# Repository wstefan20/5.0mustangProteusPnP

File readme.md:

# 5.0 Mustang Proteus PnP
PnP adapter board for 5.0 mustang EEC-IV computer using Proteus Rusefi v0.5 compatible board.

This board is designed as both a PnP stock replacement for the A9L/A9P EECs found in 5.0 manual foxbody mustangs, as well as a fully featured aftermarket ECU. This board is designed to fit into BOTH versions of the stock Ford EEC-IV case.

PLEASE do not rip apart any A9L computers to house this unit, there's very few of them left and they sell for a lot! Keep or sell that and buy any late 80s to early 90s EEC-IV as a donor instead such as 88 ford taurus 2.4 EEC for $25.

wiki and more info coming after fully tested.

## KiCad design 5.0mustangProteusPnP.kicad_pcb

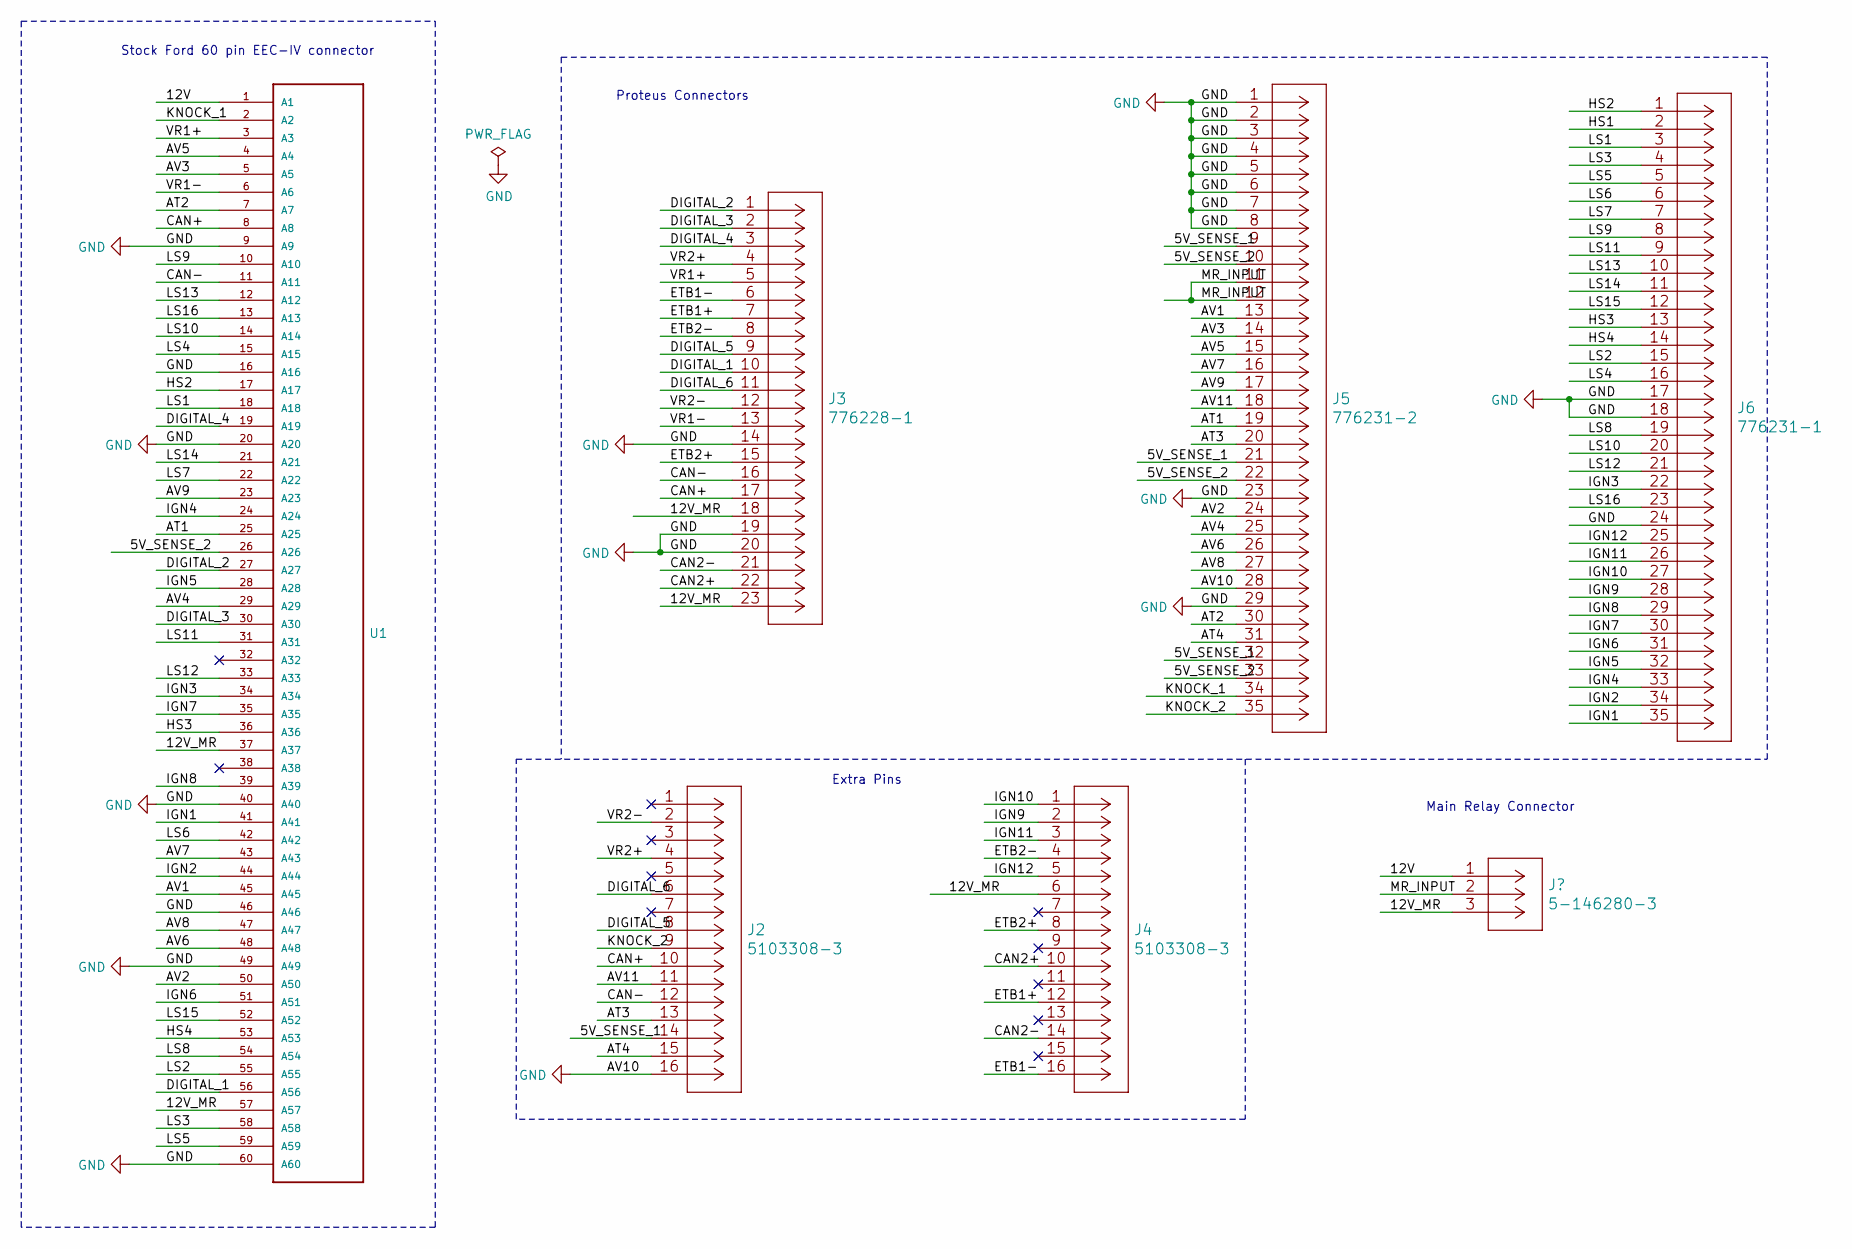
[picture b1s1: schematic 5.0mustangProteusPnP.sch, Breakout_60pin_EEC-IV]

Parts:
J2, J4: 5103308-3
J3: 776228-1
J5: 776231-2
J6: 776231-1
U1: FORD60PIN

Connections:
/5V_SENSE_1: J2.14, J5.9, J5.21, J5.32
/5V_SENSE_2: J5.10, J5.22, J5.33, U1.26 (A26)
/12V: U1.1 (A1); also elsewhere on the board
/12V_MR: J3.18, J3.23, J4.6, U1.37 (A37), U1.57 (A57); also elsewhere on the board
/AT1: J5.19, U1.25 (A25)
/AT2: J5.30, U1.7 (A7)
/AT3: J2.13, J5.20
/AT4: J2.15, J5.31
/AV1: J5.13, U1.45 (A45)
/AV2: J5.24, U1.50 (A50)
/AV3: J5.14, U1.5 (A5)
/AV4: J5.25, U1.29 (A29)
/AV5: J5.15, U1.4 (A4)
/AV6: J5.26, U1.48 (A48)
/AV7: J5.16, U1.43 (A43)
/AV8: J5.27, U1.47 (A47)
/AV9: J5.17, U1.23 (A23)
/AV11: J2.11, J5.18
/CAN2+: J3.22, J4.10
/CAN2-: J3.21, J4.14
/CAN+: J2.10, J3.17, U1.8 (A8)
/CAN-: J2.12, J3.16, U1.11 (A11)
/DIGITAL_1: J3.10, U1.56 (A56)
/DIGITAL_2: J3.1, U1.27 (A27)
/DIGITAL_3: J3.2, U1.30 (A30)
/DIGITAL_4: J3.3, U1.19 (A19)
/DIGITAL_5: J2.8, J3.9
/DIGITAL_6: J2.6, J3.11
/ETB1+: J3.7, J4.12
/ETB1-: J3.6, J4.16
/ETB2+: J3.15, J4.8
/ETB2-: J3.8, J4.4
/HS1: J2.1, J6.2
/HS3: J6.13, U1.36 (A36)
/HS4: J6.14, U1.53 (A53)
/IGN1: J6.35, U1.41 (A41)
/IGN2: J6.34, U1.44 (A44)
/IGN3: J6.22, U1.34 (A34)
/IGN4: J6.33, U1.24 (A24)
/IGN5: J6.32, U1.28 (A28)
/IGN6: J6.31, U1.51 (A51)
/IGN7: J6.30, U1.35 (A35)
/IGN8: J6.29, U1.39 (A39)
/IGN9: J4.2, J6.28
/IGN10: J4.1, J6.27
/IGN11: J4.3, J6.26
/IGN12: J4.5, J6.25
/KNOCK_1: J5.34, U1.2 (A2)
/KNOCK_2: J2.9, J5.35
/LS1: J6.3, U1.18 (A18)
/LS2: J6.15, U1.55 (A55)
/LS3: J6.4, U1.58 (A58)
/LS4: J6.16, U1.15 (A15)
/LS5: J6.5, U1.59 (A59)
/LS6: J6.6, U1.42 (A42)
/LS7: J6.7, U1.22 (A22)
/LS8: J6.19, U1.54 (A54)
/LS9: J6.8, U1.10 (A10)
/LS10: J6.20, U1.14 (A14)
/LS11: J6.9, U1.31 (A31)
/LS13: J6.10, U1.12 (A12)
/LS14: J6.11, U1.21 (A21)
/LS15: J6.12, U1.52 (A52)
/LS16: J6.23, U1.13 (A13)
/MR_INPUT: J5.11, J5.12; also elsewhere on the board
/VR1+: J3.5, U1.3 (A3)
/VR1-: J3.13, U1.6 (A6)
/VR2+: J2.4, J3.4
/VR2-: J2.2, J3.12
GND: J2.16, J3.14, J3.19, J3.20, J5.1, J5.2, J5.3, J5.4, J5.5, J5.6, J5.7, J5.8, J5.23, J5.28, J5.29, J6.17, J6.18, J6.24, U1.9 (A9), U1.16 (A16), U1.20 (A20), U1.40 (A40), U1.46 (A46), U1.49 (A49), U1.60 (A60)

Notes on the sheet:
Proteus Connectors
Stock Ford 60 pin EEC-IV connector
Extra Pins
Main Relay Connector

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
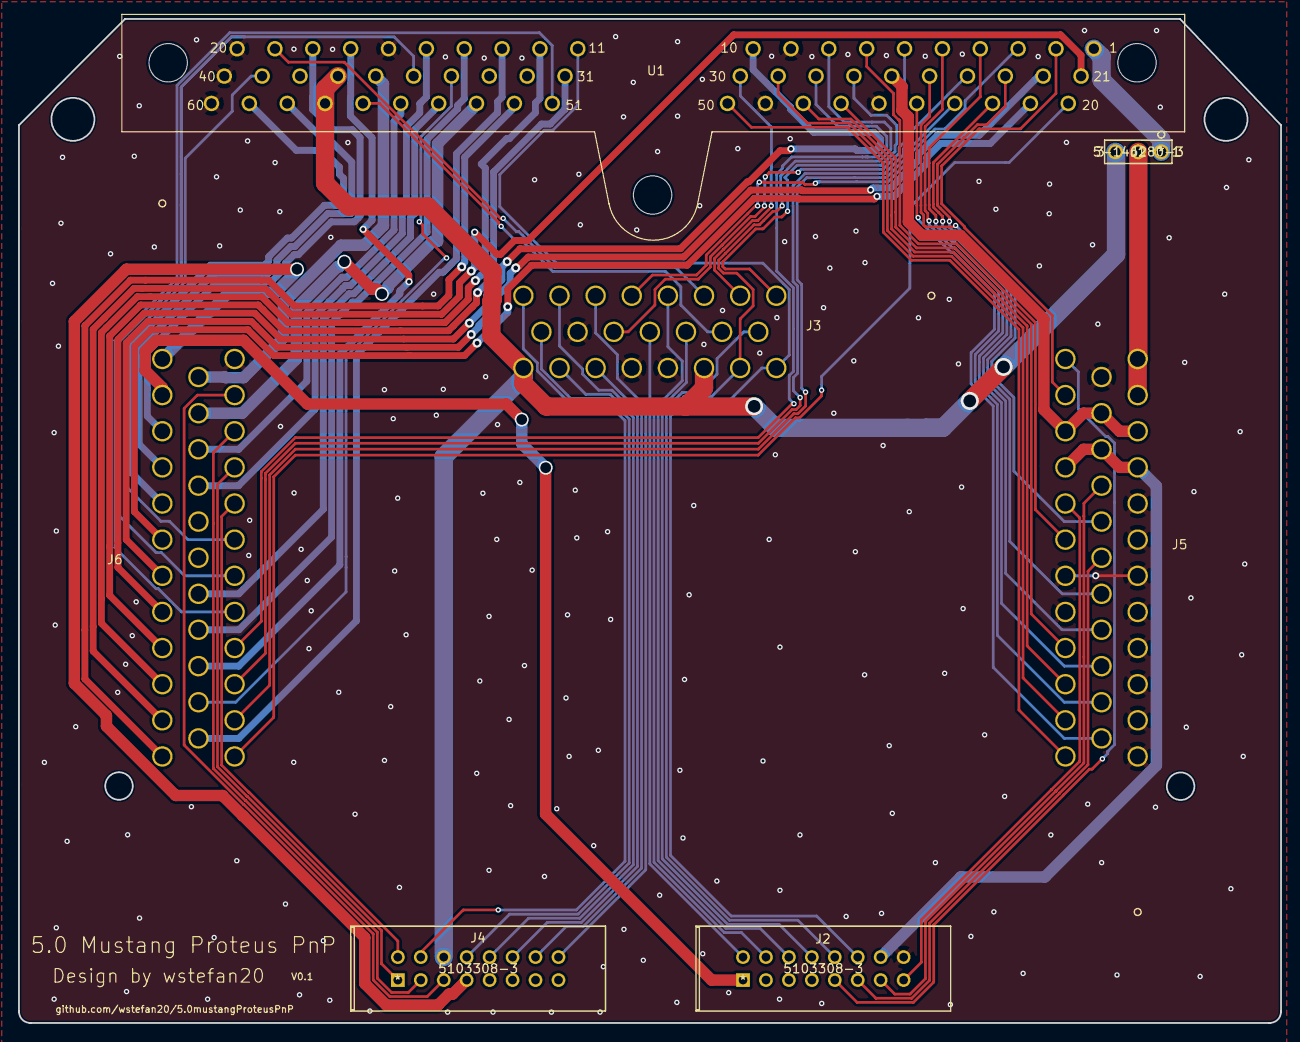
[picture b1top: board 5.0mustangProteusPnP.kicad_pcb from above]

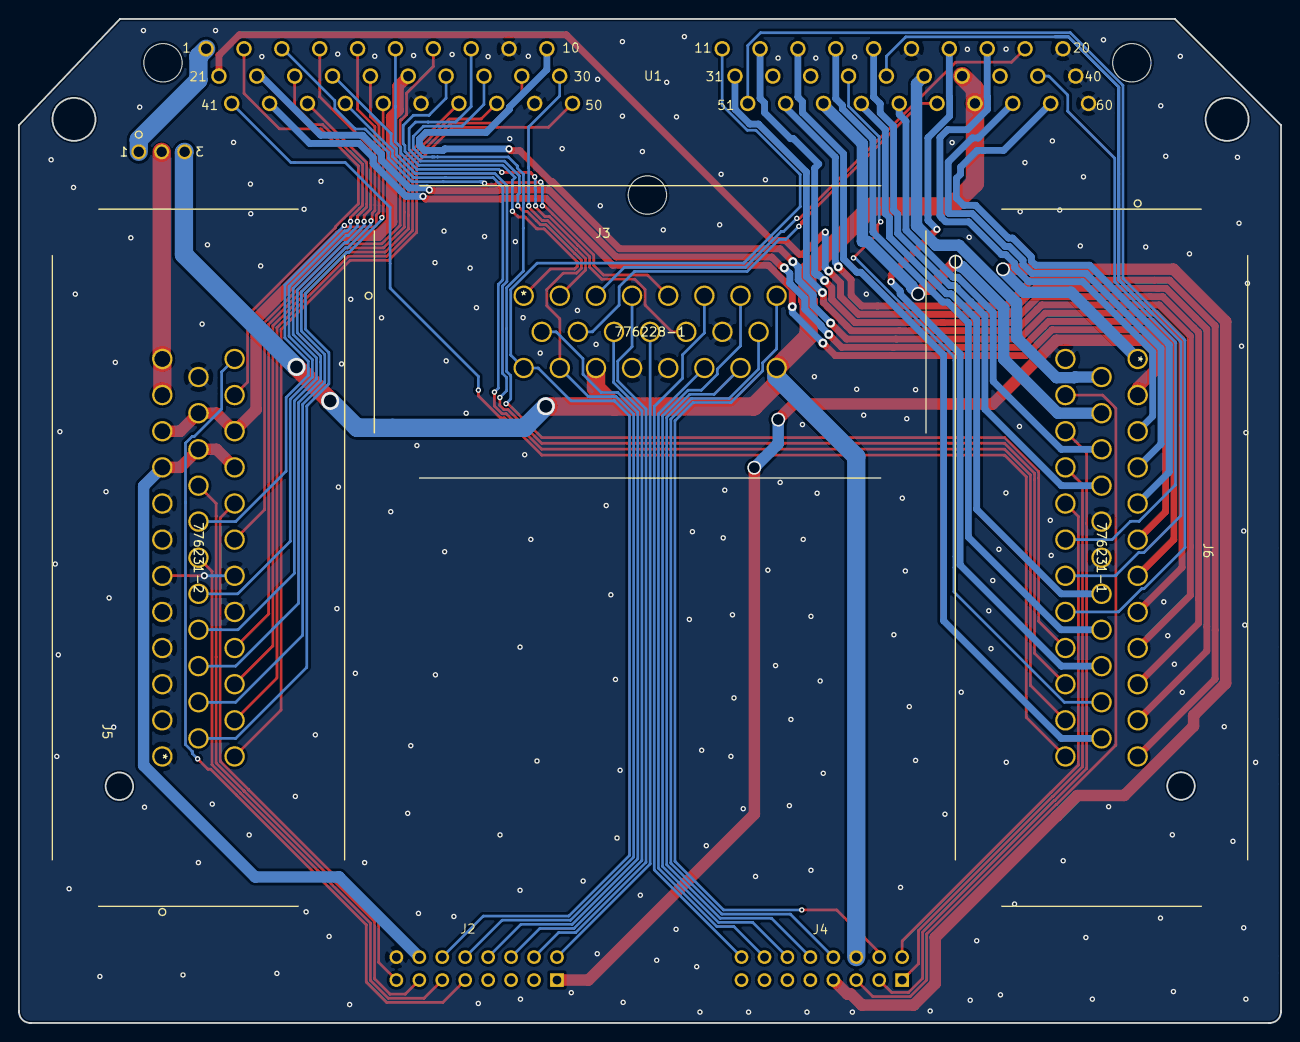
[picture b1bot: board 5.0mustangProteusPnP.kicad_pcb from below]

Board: 2 copper layers, 139.7 x 111.1 mm, 7 parts (3 on the bottom side), 72 nets.

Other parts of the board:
J1: 5-146280-3

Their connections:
/12V: J1.1; also elsewhere on the board
/12V_MR: J1.3; also elsewhere on the board
/MR_INPUT: J1.2; also elsewhere on the board

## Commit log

2021-01-08 re-routed to optimise
2021-01-08 changed 12V
2021-01-09 fixed 12V and IAC
2021-01-09 fixed CEL assign
2021-01-13 updated board outline/holes

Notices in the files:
parts and their libraries:
Copyright 2016 Accelerated Designs. All rights reserved.
